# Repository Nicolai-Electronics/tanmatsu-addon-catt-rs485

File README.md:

# Tanmatsu add-on: CATT RS-485 & RS-422 adapter

This repository contains the hardware design files for the CATT RS-485 & RS-422 adapter.

## Documentation

Need the schematic? [It's in this repository as a PDF file](schematic.pdf).

## License

This hardware design may be used under the terms of the [CERN-OHL-P](LICENSE) license.

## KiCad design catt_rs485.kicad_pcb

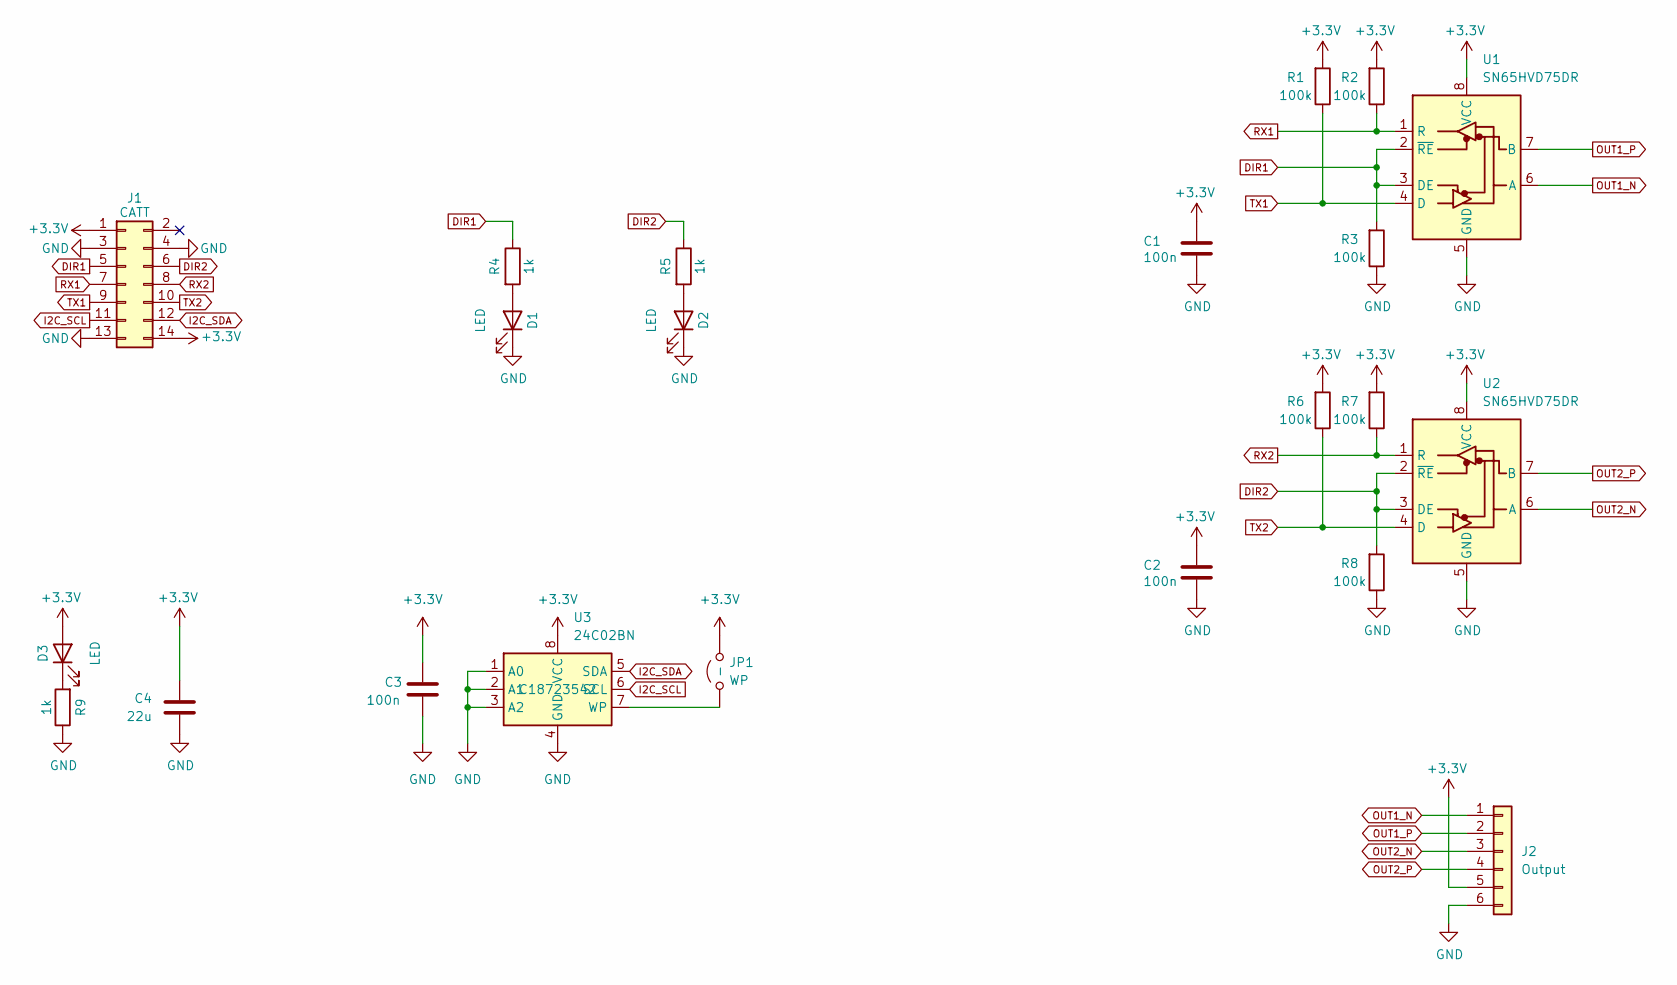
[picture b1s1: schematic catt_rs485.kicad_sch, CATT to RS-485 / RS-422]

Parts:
C1, C2, C3: 100n; C_0402_1005Metric; LCSC C307331
C4: 22u; C_0805_2012Metric; LCSC C602037
D1, D2, D3: LED; LED_0603_1608Metric; LCSC C7496820
J1: CATT; PinHeader_2x07_P2.54mm_Horizontal; LCSC C492435
J2: Output; CONN-TH_WJ15EDGRC-3.81-6P; LCSC C7246
JP1: WP; SolderJumper-2_P1.3mm_Open_TrianglePad1.0x1.5mm
R1, R2, R3, R6, R7, R8: 100k; R_0402_1005Metric; LCSC C25741
R4, R5, R9: 1k; R_0402_1005Metric; LCSC C11702
U1, U2: SN65HVD75DR; SOIC-8_3.9x4.9mm_P1.27mm; LCSC C57928
U3: 24C02BN; SOP-8_3.9x4.9mm_P1.27mm; LCSC C18723542

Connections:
+3.3V: C1.1, C2.1, C3.1, C4.1, D3.2 (A), J1.1, J1.14, J2.5, JP1.2 (B), R1.2, R2.2, R6.2, R7.2, U1.8 (VCC), U2.8 (VCC), U3.8 (VCC)
DIR1: J1.5, R3.2, R4.1, U1.2 (~RE), U1.3 (DE)
DIR2: J1.6, R5.1, R8.2, U2.2 (~RE), U2.3 (DE)
GND: C1.2, C2.2, C3.2, C4.2, D1.1 (K), D2.1 (K), J1.3, J1.4, J1.13, J2.6, R3.1, R8.1, R9.1, U1.5 (GND), U2.5 (GND), U3.1 (A0), U3.2 (A1), U3.3 (A2), U3.4 (GND)
I2C_SCL: J1.11, U3.6 (SCL)
I2C_SDA: J1.12, U3.5 (SDA)
unnamed: D1.2 (A), R4.2
unnamed: D2.2 (A), R5.2
unnamed: D3.1 (K), R9.2
unnamed: JP1.1 (A), U3.7 (WP)
OUT1_N: J2.1, U1.6 (A)
OUT1_P: J2.2, U1.7 (B)
OUT2_N: J2.3, U2.6 (A)
OUT2_P: J2.4, U2.7 (B)
RX1: J1.7, R2.1, U1.1 (R)
RX2: J1.8, R7.1, U2.1 (R)
TX1: J1.9, R1.1, U1.4 (D)
TX2: J1.10, R6.1, U2.4 (D)

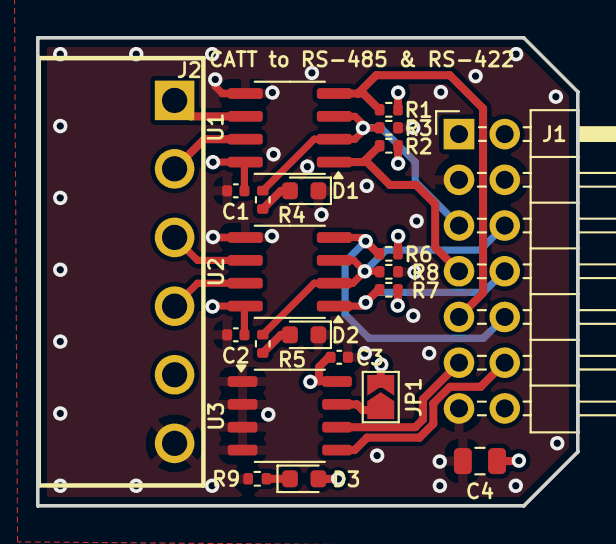
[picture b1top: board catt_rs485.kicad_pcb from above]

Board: 4 copper layers, 30.0 x 26.0 mm, 22 parts (0 on the bottom side), 18 nets.

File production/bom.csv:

Designator,Footprint,Quantity,Value,LCSC Part #
"C1, C2, C3",0402,3,100n,C307331
C4,0805,1,22u,C602037
"D1, D2, D3",0603,3,LED,C7496820
J1,PinHeader_2x07_P2.54mm_Horizontal,1,CATT,C492435
J2,CONN-TH_WJ15EDGRC-3.81-6P,1,Output,C7246
"R1, R2, R3, R6, R7, R8",0402,6,100k,C25741
"R4, R5, R9",0402,3,1k,C11702
"U1, U2",SOIC-8_3.9x4.9mm_P1.27mm,2,SN65HVD75DR,C57928
U3,SOP-8_3.9x4.9mm_P1.27mm,1,24C02BN,C18723542

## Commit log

2025-05-17 Renumber components
2025-05-17 Add missing LCSC number of output connector
